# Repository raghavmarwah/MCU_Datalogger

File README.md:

# ATMEGA328P based datalogger

This is project #2 for the course [KiCAD like a Pro](https://techexplorations.com/so/kicad-like-a-pro-3rd-edition/). In this project, I created a PCB design for a ATMEGA328P based datalogger that stores data to two EEPROMS. This is only the hardware design in KiCad, no actual coding of the MCU done in this project.
<br><br>
More information about my progress with the course: https://raghavmarwah.com/kicad-udemy-course/
<br>

## Schematics

## 2 layer PCB

## 4 layer PCB

## 3D render (2 layer) (front)

## 3D render (2 layer) (rear)

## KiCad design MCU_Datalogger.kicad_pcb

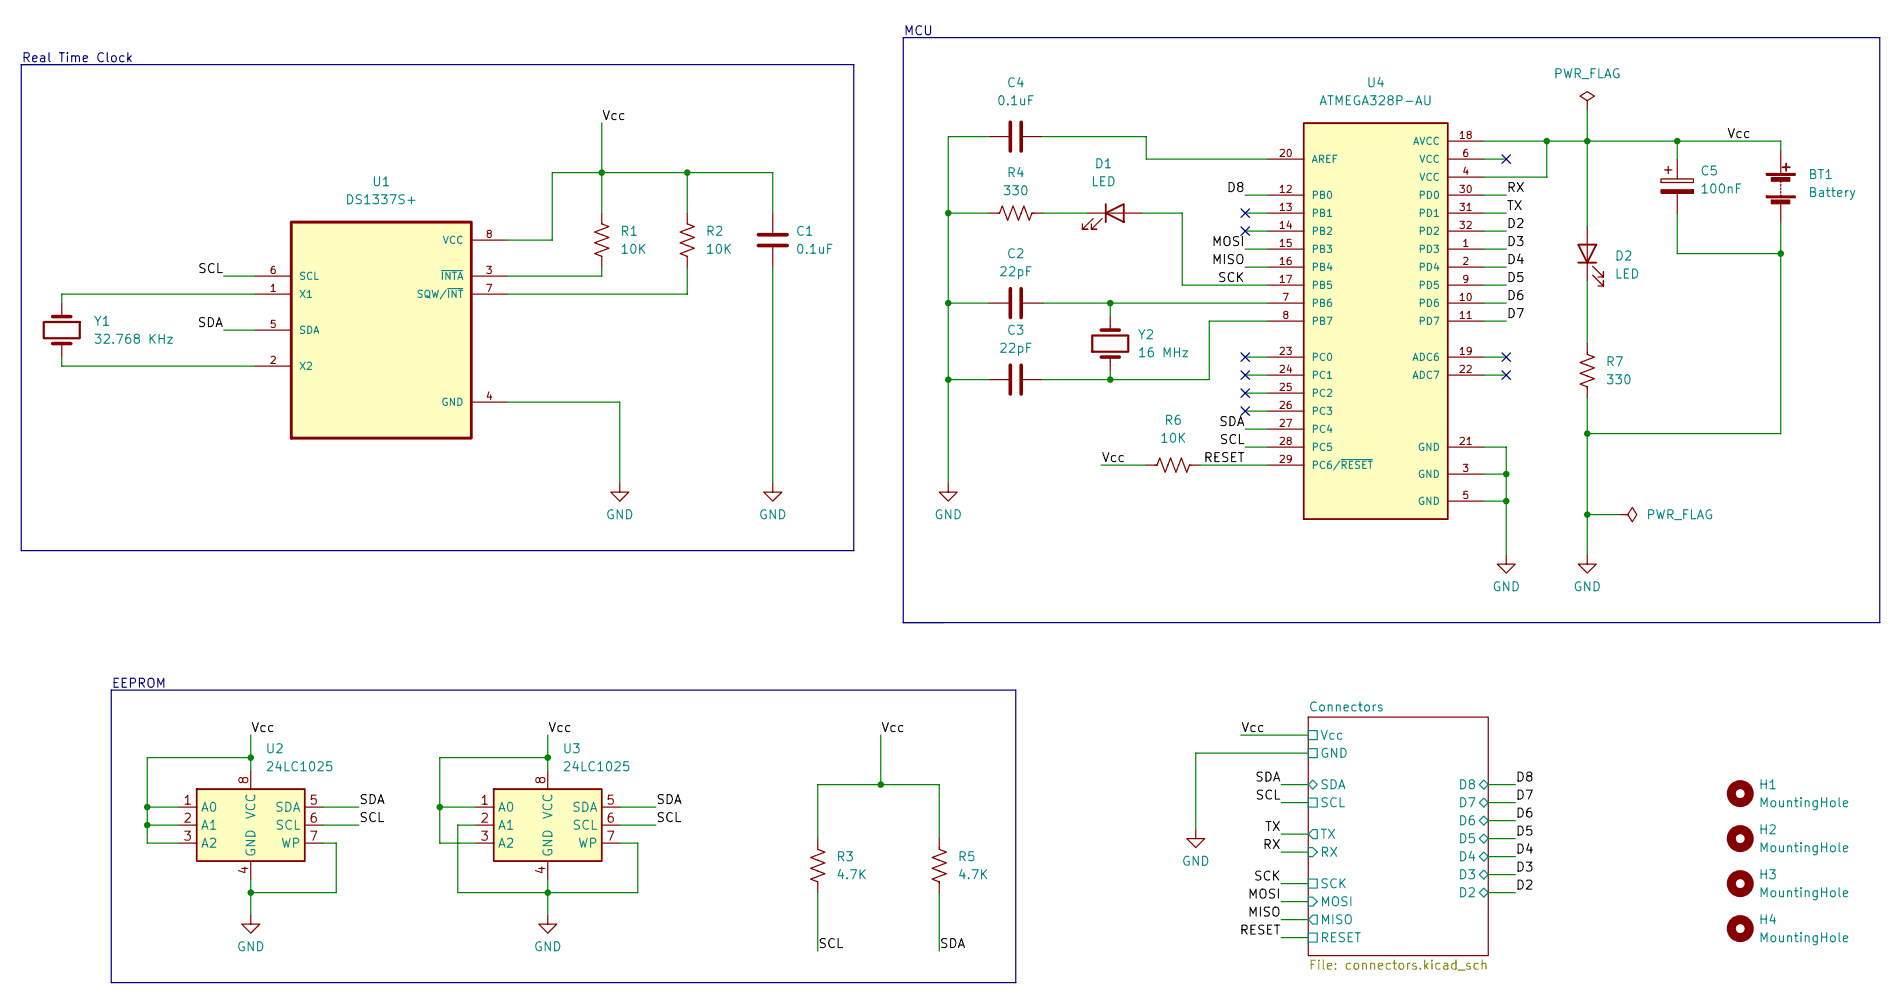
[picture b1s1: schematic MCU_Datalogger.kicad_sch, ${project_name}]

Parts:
BT1: Battery; PinHeader_1x02_P2.54mm_Vertical
C1, C4: 0.1uF; C_0805_2012Metric_Pad1.18x1.45mm_HandSolder
C2, C3: 22pF; C_0805_2012Metric_Pad1.18x1.45mm_HandSolder
C5: 100nF; C_0805_2012Metric_Pad1.18x1.45mm_HandSolder
D1, D2: LED; LED_0805_2012Metric_Pad1.15x1.40mm_HandSolder
H1, H2, H3, H4: MountingHole; MountingHole_2.1mm
R1, R2, R6: 10K; R_0805_2012Metric_Pad1.20x1.40mm_HandSolder
R3, R5: 4.7K; R_0805_2012Metric_Pad1.20x1.40mm_HandSolder
R4, R7: 330; R_0805_2012Metric_Pad1.20x1.40mm_HandSolder
U1: DS1337S+; SOIC127P600X175-8N
U2, U3: 24LC1025; SOIC-8_5.23x5.23mm_P1.27mm
U4: ATMEGA328P-AU; QFP80P900X900X120-32N
Y1: 32.768 KHz; XTAL_ABM2-32.000MHZ-D4YF-T
Y2: 16 MHz; XTAL_ABM2-32.000MHZ-D4YF-T

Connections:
/D2: U4.32 (PD2); also elsewhere on the board
/D3: U4.1 (PD3); also elsewhere on the board
/D4: U4.2 (PD4); also elsewhere on the board
/D5: U4.9 (PD5); also elsewhere on the board
/D6: U4.10 (PD6); also elsewhere on the board
/D7: U4.11 (PD7); also elsewhere on the board
/D8: U4.12 (PB0); also elsewhere on the board
/MISO: U4.16 (PB4); also elsewhere on the board
/MOSI: U4.15 (PB3); also elsewhere on the board
/RESET: R6.2, U4.29 (PC6/~RESET); also elsewhere on the board
/RX: U4.30 (PD0); also elsewhere on the board
/SCK: D1.2 (A), U4.17 (PB5); also elsewhere on the board
/SCL: R3.2, U1.6 (SCL), U2.6 (SCL), U3.6 (SCL), U4.28 (PC5); also elsewhere on the board
/SDA: R5.2, U1.5 (SDA), U2.5 (SDA), U3.5 (SDA), U4.27 (PC4); also elsewhere on the board
/TX: U4.31 (PD1); also elsewhere on the board
/Vcc: BT1.1 (+), C1.1, C5.1, D2.2 (A), R1.1, R2.1, R3.1, R5.1, R6.1, U1.8 (VCC), U2.1 (A0), U2.2 (A1), U2.3 (A2), U2.8 (VCC), U3.1 (A0), U3.3 (A2), U3.8 (VCC), U4.4 (VCC), U4.18 (AVCC); also elsewhere on the board
GND: BT1.2 (-), C1.2, C2.1, C3.1, C4.1, C5.2, R4.1, R7.2, U1.4 (GND), U2.4 (GND), U2.7 (WP), U3.2 (A1), U3.4 (GND), U3.7 (WP), U4.3 (GND), U4.5 (GND), U4.21 (GND); also elsewhere on the board
unnamed: C2.2, U4.7 (PB6), Y2.2
unnamed: C3.2, U4.8 (PB7), Y2.1
unnamed: C4.2, U4.20 (AREF)
unnamed: D1.1 (K), R4.2
unnamed: D2.1 (K), R7.1
unnamed: R1.2, U1.3 (~INTA)
unnamed: R2.2, U1.7 (SQW/~INT)
unnamed: U1.1 (X1), Y1.1
unnamed: U1.2 (X2), Y1.2

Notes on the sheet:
EEPROM
MCU
Real Time Clock

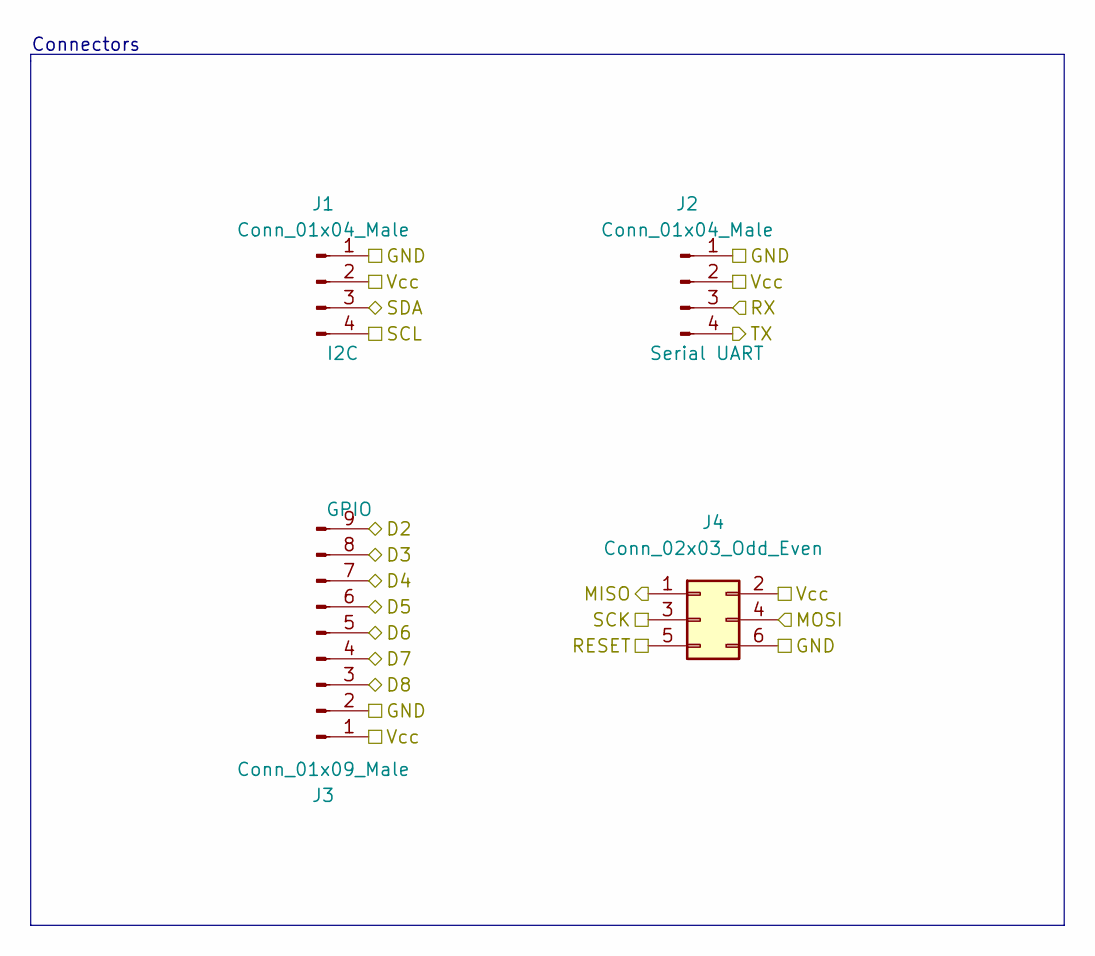
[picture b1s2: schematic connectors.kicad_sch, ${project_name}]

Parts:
J1, J2: Conn_01x04_Male; PinHeader_1x04_P2.54mm_Vertical
J3: Conn_01x09_Male; PinHeader_1x09_P2.54mm_Vertical
J4: Conn_02x03_Odd_Even; PinHeader_2x03_P2.54mm_Vertical

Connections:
/D2: J3.9; also elsewhere on the board
/D3: J3.8; also elsewhere on the board
/D4: J3.7; also elsewhere on the board
/D5: J3.6; also elsewhere on the board
/D6: J3.5; also elsewhere on the board
/D7: J3.4; also elsewhere on the board
/D8: J3.3; also elsewhere on the board
/MISO: J4.1; also elsewhere on the board
/MOSI: J4.4; also elsewhere on the board
/RESET: J4.5; also elsewhere on the board
/RX: J2.3; also elsewhere on the board
/SCK: J4.3; also elsewhere on the board
/SCL: J1.4; also elsewhere on the board
/SDA: J1.3; also elsewhere on the board
/TX: J2.4; also elsewhere on the board
/Vcc: J1.2, J2.2, J3.1, J4.2; also elsewhere on the board
GND: J1.1, J2.1, J3.2, J4.6; also elsewhere on the board

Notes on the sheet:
Connectors

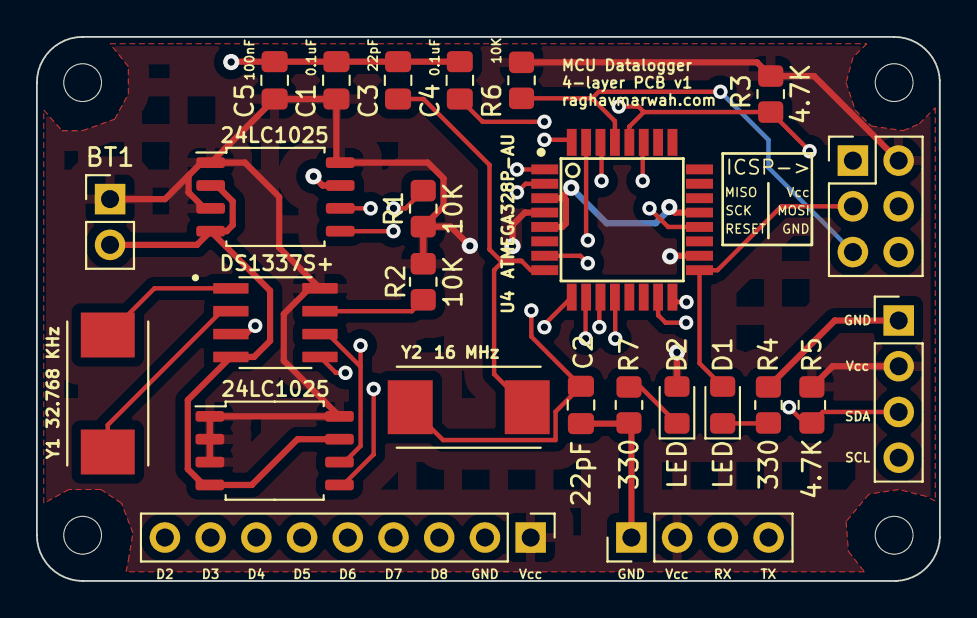
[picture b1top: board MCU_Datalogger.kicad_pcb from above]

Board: 4 copper layers, 50.2 x 30.2 mm, 29 parts (0 on the bottom side), 26 nets.

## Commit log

2022-08-29 Created KiCad project
2022-08-29 Added required components to the schematic sheets
2022-08-30 Schematic design complete
2022-08-30 2 layer PCB design complete
2022-08-30 Added .gitattributes file to ignore pcb file during merge
2022-08-30 Minor changes to PCB footprints
2022-08-30 Added SCL net to schematic and fixed errors
2022-08-30 Test commit, deleted tracks and vias
2022-08-30 4 layer PCB design complete
2022-09-04 Created README.md file
